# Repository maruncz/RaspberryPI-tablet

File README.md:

RaspberryPI-tablet

just clean project

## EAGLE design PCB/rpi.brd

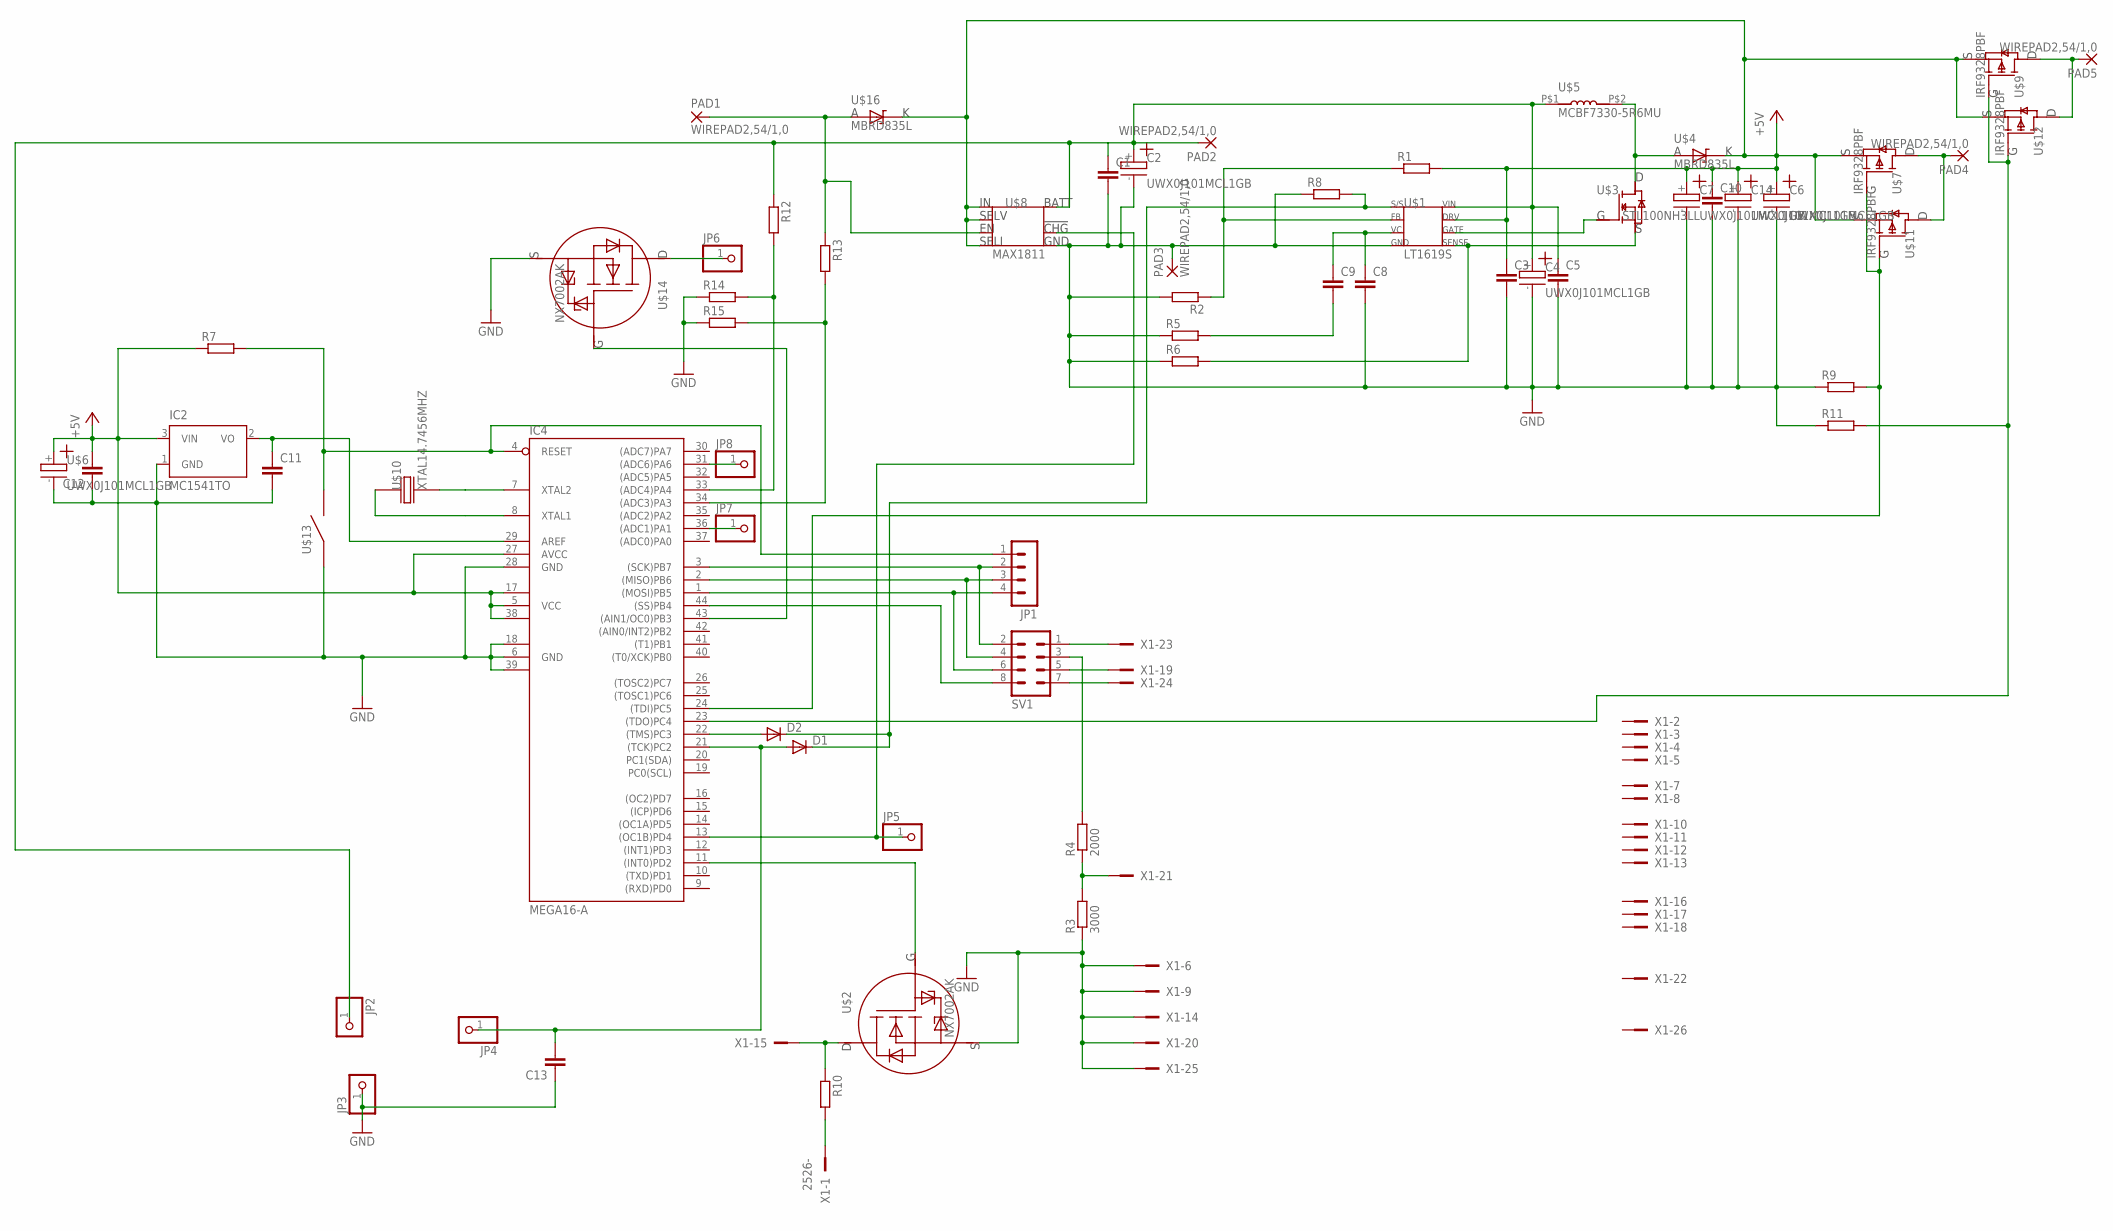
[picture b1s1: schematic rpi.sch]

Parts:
C1, C3, C5, C8, C9, C10, C11, C12, C13: C-EUC1206; C1206
C2, C4, C6, C7, C14: UWX0J101MCL1GB
D1, D2: DIODE-MINIMELF; MINIMELF
IC2: MC1541TO; TO92
IC4: MEGA16-A; TQFP44
JP1: MA04-1
JP2, JP3, JP4, JP5, JP6, JP7, JP8: PINHD-1X1; 1X01
PAD1, PAD2, PAD3, PAD4, PAD5: WIREPAD2,54/1,0; 2,54/1,0
R1, R2, R5, R6, R7, R8, R9, R10, R11, R12, R13, R14, R15: R-EU_R1206; R1206
R3: 3000; R1206
R4: 2000; R1206
SV1: MA04-2
U$1: LT1619S; SO8
U$2, U$14: NX7002AK; SOT23
U$3: STL100NH3LL; POWERFLAT6X5
U$4, U$16: MBRD835L; DPAK
U$5: MCBF7330-5R6MU
U$6: UWX0J101MCL1GB
U$7, U$9, U$11, U$12: IRF9328PBF; SO8
U$8: MAX1811; SO8
U$10: XTAL14.7456MHZ; HC49-SMD
U$13: TLACITKO
X1: 2526-; PAK100/2500-26

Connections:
+5V: C3.1, C6.+, C7.+, C10.1, C12.2, C14.+, IC2.3 (VIN), IC4.5 (VCC), IC4.17 (VCC1), IC4.27 (AVCC), IC4.38 (VCC2), R1.2, R7.1, U$1.D2 (DRV), U$4.4 (K), U$6.+, U$7.S, U$7.S2 (S), U$7.S3 (S), U$8.G (IN), U$8.S (SELV), U$8.S2 (SELI), U$9.S, U$9.S2 (S), U$9.S3 (S), U$11.S, U$11.S2 (S), U$11.S3 (S), U$12.S, U$12.S2 (S), U$12.S3 (S), U$16.4 (K)
AREF: C11.1, IC2.2 (VO), IC4.29 (AREF)
GND: C1.2, C2.-, C3.2, C4.-, C5.2, C6.-, C7.-, C8.2, C10.2, C11.2, C12.1, C13.1, C14.-, IC2.1 (GND), IC4.6 (GND), IC4.18 (GND1), IC4.28 (GND), IC4.39 (GND2), JP3.1, PAD3.1, R2.2, R3.1, R5.1, R6.1, R8.1, R9.1, R11.1, R14.1, R15.1, U$1.G (GND), U$2.S, U$6.-, U$8.D3 (GND), U$8.S3 (GND), U$13.P$1, U$13.P$3, U$14.S, X1.6, X1.9, X1.14, X1.20, X1.25
unnamed: R3.2, R4.1, X1.21
unnamed: IC4.34 ((ADC3)PA3), R13.2, R15.2
unnamed: D2.A, IC4.22 ((TMS)PC3)
unnamed: R4.2, SV1.3
unnamed: SV1.7, X1.24
unnamed: IC4.11 ((INT0)PD2), U$2.G
unnamed: R10.2, X1.1
unnamed: R10.1, U$2.D, X1.15
unnamed: IC4.43 ((AIN1/OC0)PB3), U$14.G
unnamed: JP6.1, U$14.D
unnamed: IC4.36 ((ADC1)PA1), JP7.1
unnamed: R1.1, R2.1, U$1.S2 (FB)
unnamed: R6.2, U$1.D4 (SENSE), U$3.1 (S), U$3.2 (S), U$3.3 (S)
unnamed: IC4.31 ((ADC6)PA6), JP8.1
unnamed: IC4.24 ((TDI)PC5), R9.2, U$7.G, U$11.G
unnamed: IC4.33 ((ADC4)PA4), R12.2, R14.2
unnamed: PAD1.1, R13.1, U$8.D2 (EN), U$16.1 (A), U$16.3 (A)
unnamed: U$1.D3 (GATE), U$3.4 (G)
unnamed: C13.2, D1.A, IC4.21 ((TCK)PC2), JP4.1
unnamed: PAD4.1, U$7.D, U$7.D2 (D), U$7.D3 (D), U$7.D4 (D), U$11.D, U$11.D2 (D), U$11.D3 (D), U$11.D4 (D)
unnamed: SV1.5, X1.19
unnamed: SV1.1, X1.23
unnamed: U$3.5 (D), U$4.1 (A), U$4.3 (A), U$5.P$2
unnamed: C9.2, R5.2
unnamed: C8.1, C9.1, U$1.S3 (VC)
unnamed: PAD5.1, U$9.D, U$9.D2 (D), U$9.D3 (D), U$9.D4 (D), U$12.D, U$12.D2 (D), U$12.D3 (D), U$12.D4 (D)
PA3: C1.1, C2.+, C4.+, C5.1, JP2.1, PAD2.1, R12.1, U$1.D (VIN), U$5.P$1, U$8.D4 (BATT)
PB4: IC4.44 ((SS)PB4), SV1.8
PB5: IC4.1 ((MOSI)PB5), JP1.4, SV1.6
PB6: IC4.2 ((MISO)PB6), JP1.3, SV1.4
PC3: D1.C, D2.C, R8.2, U$1.S (S/S)
PC4: IC4.23 ((TDO)PC4), R11.2, U$9.G, U$12.G
PD5: IC4.13 ((OC1B)PD4), JP5.1, U$8.D (!CHG)
RESET: IC4.4 (RESET), JP1.1, R7.2, U$13.P$2, U$13.P$4
SCK: IC4.3 ((SCK)PB7), JP1.2, SV1.2
XTAL1: IC4.8 (XTAL1), U$10.P$1
XTAL2: IC4.7 (XTAL2), U$10.P$2

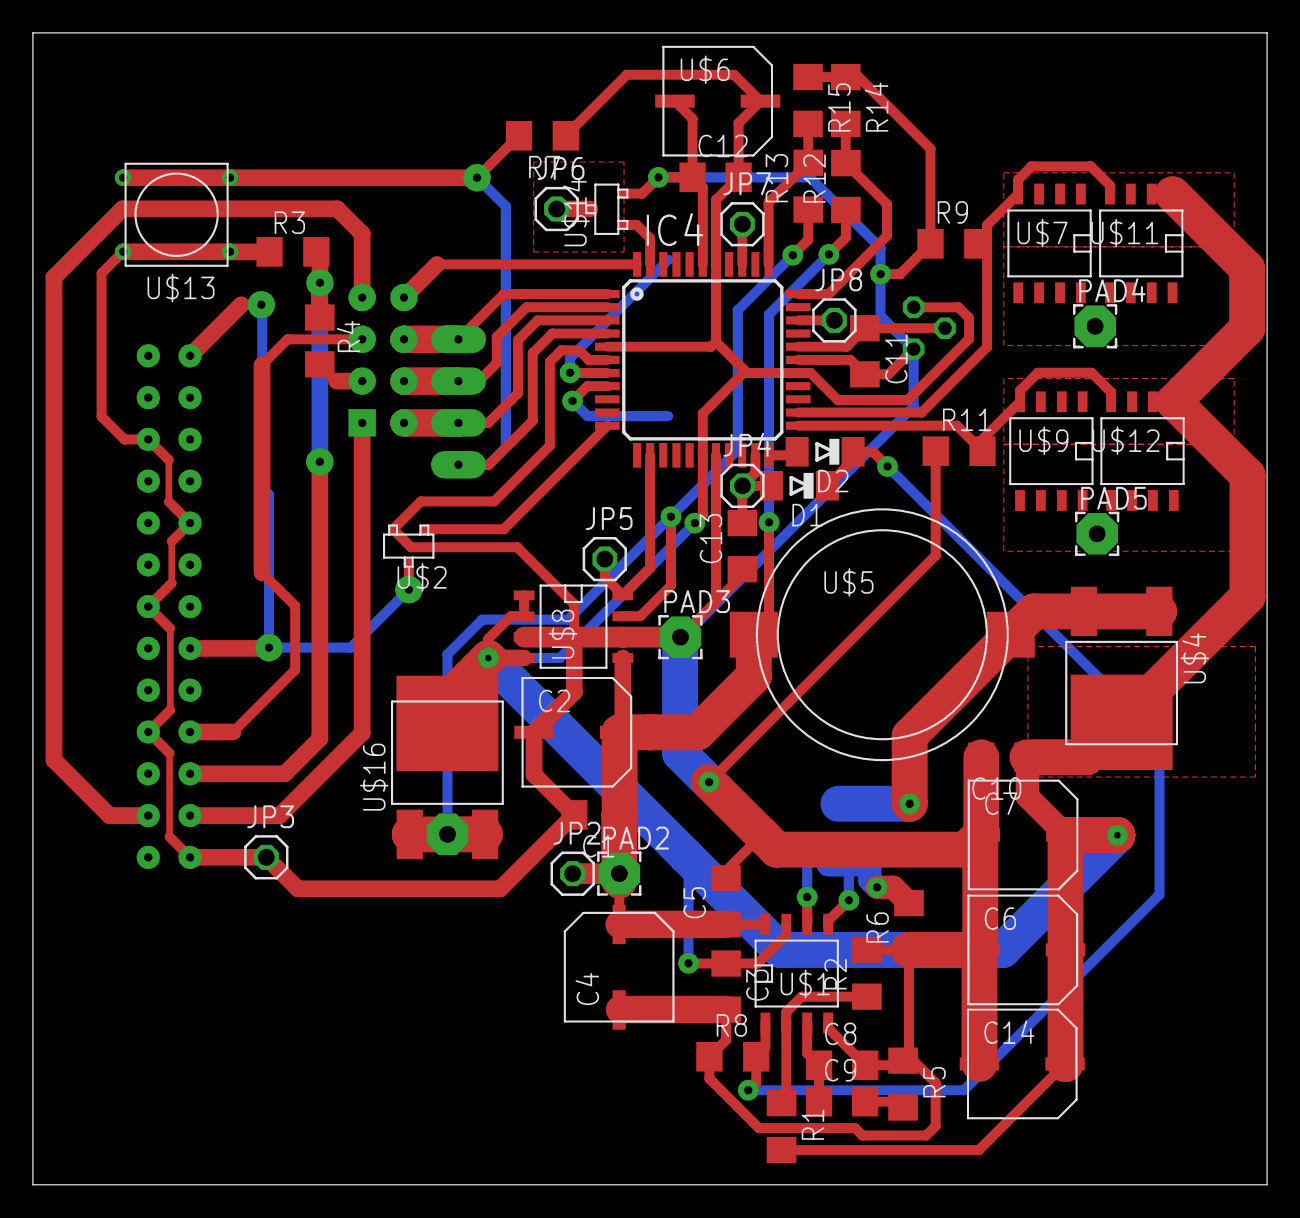
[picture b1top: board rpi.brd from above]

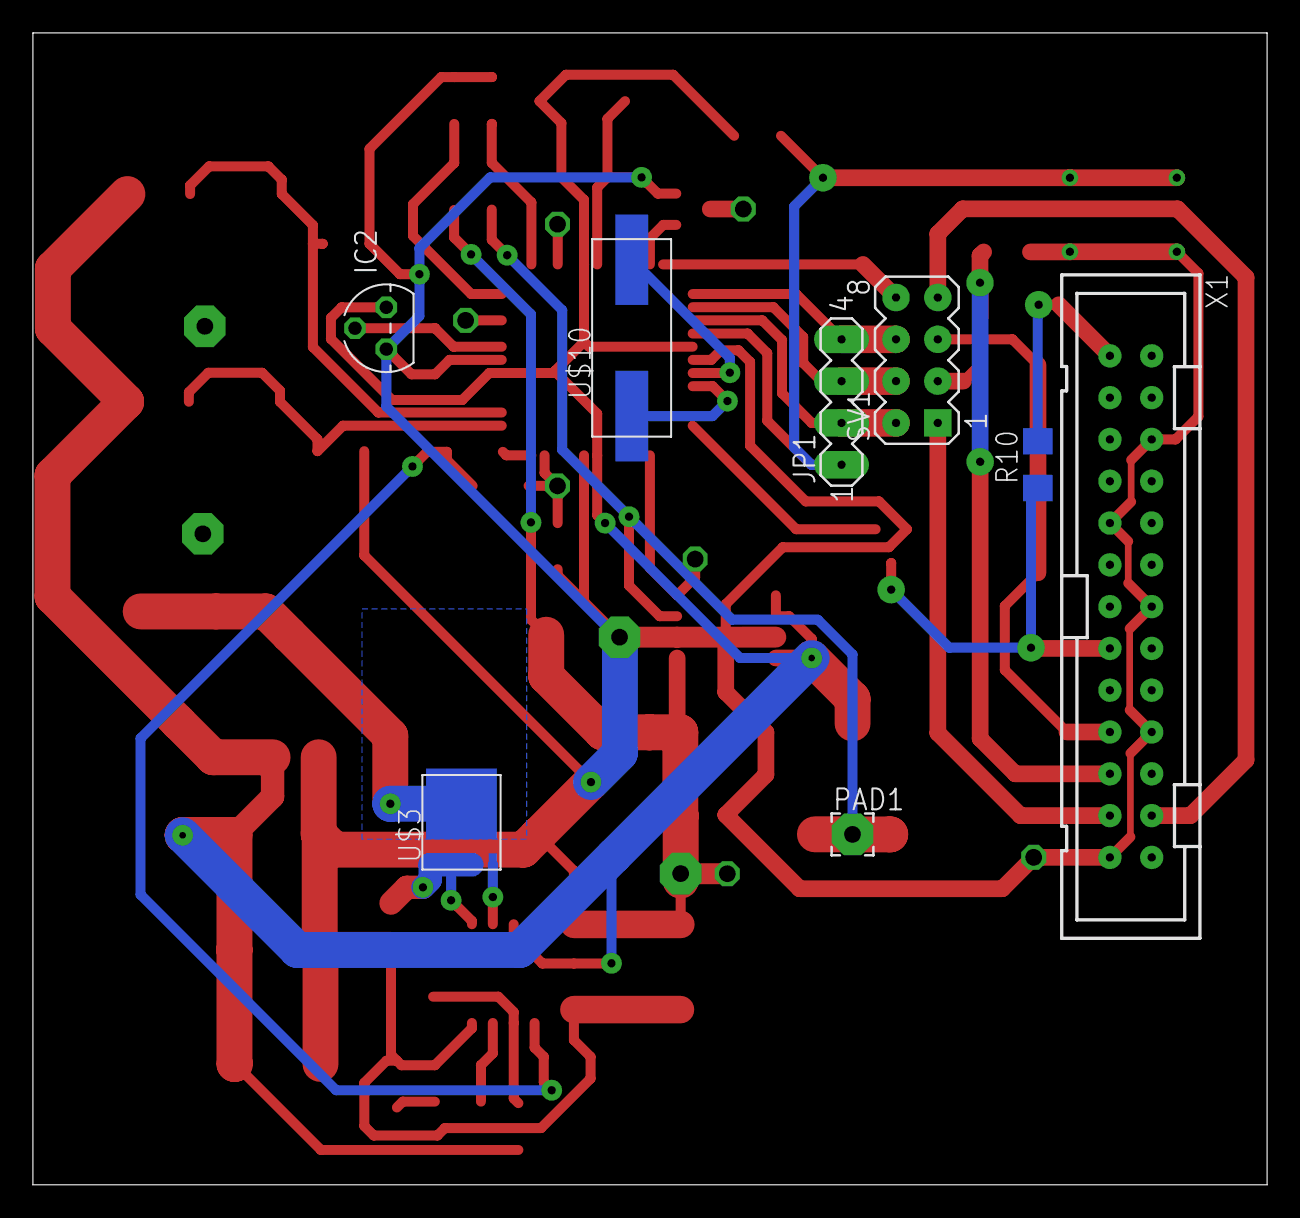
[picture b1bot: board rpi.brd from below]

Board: 2 copper layers, 75.0 x 70.0 mm, 63 parts (8 on the bottom side), 40 nets.

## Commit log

2014-02-09 Initial commit
    Changes to be committed:
    (use "git rm --cached <file>..." to unstage)
    new file: AVR/AVR.cbp
    new file: AVR/AVR.layout
    new file: AVR/Makefile
    new file: AVR/Makefile~
2014-02-09 On branch master Changes to be committed: (use "git reset HEAD <file>..." to unstage)
    new file: README.md
2014-02-09 On branch master Changes to be committed: (use "git reset HEAD <file>..." to unstage)
    modified: README.md
    Untracked files:
    (use "git add <file>..." to include in what will be committed)
    README.md~
2014-02-09 On branch master Changes to be committed: new file: RaspberryPI/Crystal_button_cancel.svg new file: RaspberryPI/Ps_GreekCross.svg modified: RaspberryPI/RaspberryPI.pro modified: RaspberryPI/Raspberry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
    Changes not staged for commit:
    deleted: AVR/Makefile~
    deleted: AVR/bin/Release/AVR.eep
    deleted: AVR/bin/Release/AVR.elf
    deleted: AVR/bin/Release/AVR.hex
    deleted: AVR/bin/Release/AVR.lock
2014-02-09 On branch master modified: RaspberryPI/RaspberryPI.pro.user modified: RaspberryPI/main.cpp modified: RaspberryPI/mainwindow.cpp modified: RaspberryPI/mainwindow.h modified: RaspberryPI/mainwindow.ui
2014-02-09 On branch master Changes to be committed: modified: AVR/main.c
2014-02-09 On branch master modified: RaspberryPI/mainwindow.cpp modified: RaspberryPI/mainwindow.h modified: RaspberryPI/mainwindow.ui
2014-02-09 On branch master modified: AVR/Makefile modified: AVR/Makefile~ deleted: AVR/bin/Release/AVR.eep deleted: AVR/bin/Release/AVR.elf deleted: AVR/bin/Release/AVR.hex deleted: AVR/bin/Release/AVR.lock de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
2014-02-09 On branch master deleted: AVR/Makefile~ modified: RaspberryPI/RaspberryPI.pro.user modified: RaspberryPI/mainwindow.cpp modified: RaspberryPI/mainwindow.h
2014-02-09 On branch master deleted: AVR/Makefile~ modified: RaspberryPI/mainwindow.cpp modified: RaspberryPI/mainwindow.h
2014-02-10 On branch master modified: RaspberryPI/RaspberryPI.pro.user modified: RaspberryPI/mainwindow.cpp modified: RaspberryPI/mainwindow.h
2014-02-10 On branch master modified: RaspberryPI/RaspberryPI.pro.user modified: RaspberryPI/mainwindow.h
2014-02-10 On branch master modified: AVR/AVR.layout modified: AVR/main.c
2014-02-10 On branch master modified: RaspberryPI/mainwindow.cpp
2014-02-10 On branch master modified: RaspberryPI/RaspberryPI.pro.user modified: RaspberryPI/mainwindow.cpp modified: RaspberryPI/mainwindow.ui
2014-02-10 On branch master modified: AVR/main.c
2014-02-11 On branch master modified: AVR/AVR.cbp modified: AVR/AVR.layout
2014-02-11 On branch master modified: RaspberryPI/RaspberryPI.pro.user modified: RaspberryPI/mainwindow.cpp
2014-02-22 On branch master modified: RaspberryPI/RaspberryPI.pro.user modified: RaspberryPI/mainwindow.cpp modified: RaspberryPI/mainwindow.h modified: RaspberryPI/mainwindow.ui
2014-02-22 On branch master modified: RaspberryPI/RaspberryPI.pro.user new file: rpi/eagle.epf new file: rpi/rpi.brd new file: rpi/rpi.pro new file: rpi/rpi.sch new file: tablet.lbr
2014-02-22 On branch master renamed: rpi/eagle.epf -> PCB/eagle.epf renamed: rpi/rpi.brd -> PCB/rpi.brd renamed: rpi/rpi.pro -> PCB/rpi.pro renamed: rpi/rpi.sch -> PCB/rpi.sch
2014-02-23 On branch master modified: PCB/eagle.epf modified: PCB/rpi.brd modified: PCB/rpi.sch modified: RaspberryPI/RaspberryPI.pro.user
2014-02-28 On branch master modified: PCB/eagle.epf modified: PCB/rpi.brd modified: RaspberryPI/RaspberryPI.pro.user modified: RaspberryPI/mainwindow.cpp
2014-03-02 On branch master modified: AVR/AVR.layout modified: AVR/Makefile
2014-03-02 On branch master modified: PCB/eagle.epf modified: PCB/rpi.brd modified: RaspberryPI/RaspberryPI.pro.user
2014-03-04 On branch master modified: PCB/eagle.epf modified: RaspberryPI/RaspberryPI.pro.user modified: RaspberryPI/mainwindow.cpp
2014-03-06 On branch master modified: PCB/eagle.epf new file: RaspberryPI-shutdown/RaspberryPI-shutdown.pro new file: RaspberryPI-shutdown/main.cpp modified: RaspberryPI/RaspberryPI.pro.user modified: Raspberry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
2014-03-06 On branch master modified: RaspberryPI-shutdown/RaspberryPI-shutdown.pro deleted: RaspberryPI/RaspberryPI.pro.user
2014-03-08 On branch master modified: PCB/eagle.epf modified: PCB/rpi.brd modified: PCB/rpi.sch modified: RaspberryPI/mainwindow.cpp modified: RaspberryPI/mainwindow.h modified: RaspberryPI/mainwindow.ui
2014-03-08 On branch master modified: PCB/eagle.epf modified: PCB/rpi.brd modified: PCB/rpi.sch
2014-03-16 On branch master modified: PCB/eagle.epf modified: PCB/rpi.brd modified: PCB/rpi.sch modified: RaspberryPI-shutdown/RaspberryPI-shutdown.pro modified: RaspberryPI/RaspberryPI.pro
2014-03-18 On branch master modified: PCB/eagle.epf modified: RaspberryPI-shutdown/main.cpp modified: RaspberryPI/RaspberryPI.pro new file: RaspberryPI/info_screen.cpp new file: RaspberryPI/info_screen.h new fi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
2014-03-18 On branch master modified: RaspberryPI/RaspberryPI.pro new file: RaspberryPI/hwinfo.cpp new file: RaspberryPI/hwinfo.h modified: RaspberryPI/info_screen.cpp modified: RaspberryPI/info_screen.h modifi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
2014-03-18 On branch master modified: RaspberryPI/hwinfo.h modified: RaspberryPI/info_screen.cpp modified: RaspberryPI/info_screen.h
2014-03-18 On branch master modified: RaspberryPI/hwinfo.cpp modified: RaspberryPI/hwinfo.h modified: RaspberryPI/info_screen.cpp modified: RaspberryPI/info_screen.h
2014-03-18 On branch master modified: RaspberryPI/hwinfo.cpp modified: RaspberryPI/hwinfo.h modified: RaspberryPI/info_screen.cpp modified: RaspberryPI/mainwindow.cpp
2014-03-18 On branch master modified: RaspberryPI/hwinfo.cpp
2014-03-23 On branch master modified: PCB/eagle.epf modified: RaspberryPI/hwinfo.cpp modified: RaspberryPI/info_screen.cpp modified: RaspberryPI/info_screen.h modified: RaspberryPI/mainwindow.cpp modified: Rasp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
2014-03-26 On branch master modified: PCB/eagle.epf modified: RaspberryPI/hwinfo.cpp modified: RaspberryPI/hwinfo.h modified: RaspberryPI/info_screen.cpp modified: RaspberryPI/mainwindow.cpp
2014-03-29 On branch master modified: RaspberryPI/RaspberryPI.pro modified: RaspberryPI/hwinfo.h new file: RaspberryPI/idle_detect.cpp new file: RaspberryPI/idle_detect.h modified: RaspberryPI/info_screen.cpp m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
2014-03-29 On branch master modified: RaspberryPI/idle_detect.cpp modified: RaspberryPI/idle_detect.h modified: RaspberryPI/mainwindow.cpp modified: RaspberryPI/mainwindow.h modified: RaspberryPI/mainwindow.ui
2014-03-30 On branch master modified: PCB/eagle.epf modified: RaspberryPI/rpi.cpp modified: RaspberryPI/rpi.h
2014-04-06 On branch master modified: PCB/eagle.epf modified: RaspberryPI/idle_detect.cpp modified: RaspberryPI/idle_detect.h modified: RaspberryPI/info_screen.ui modified: RaspberryPI/mainwindow.cpp modified: 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
2014-04-12 On branch master modified: PCB/eagle.epf modified: RaspberryPI/mainwindow.cpp modified: RaspberryPI/mainwindow.h modified: RaspberryPI/mainwindow.ui modified: RaspberryPI/rpi.cpp modified: RaspberryP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
2014-04-12 On branch master modified: RaspberryPI/RaspberryPI.pro modified: RaspberryPI/mainwindow.cpp modified: RaspberryPI/rpi.cpp modified: RaspberryPI/rpi.h
2014-04-13 On branch master modified: RaspberryPI/mainwindow.cpp modified: RaspberryPI/mainwindow.h modified: RaspberryPI/rpi.cpp modified: RaspberryPI/rpi.h
2014-04-15 On branch master modified: RaspberryPI/mainwindow.cpp modified: RaspberryPI/mainwindow.h
2014-04-21 On branch master modified: PCB/eagle.epf modified: RaspberryPI/mainwindow.cpp modified: RaspberryPI/mainwindow.h modified: RaspberryPI/rpi.cpp modified: RaspberryPI/rpi.h
2014-04-27 On branch master modified: AVR/AVR.layout modified: AVR/Makefile modified: AVR/main.c
2014-04-27 On branch master modified: PCB/eagle.epf modified: RaspberryPI/idle_detect.cpp modified: RaspberryPI/idle_detect.h modified: RaspberryPI/mainwindow.cpp modified: RaspberryPI/mainwindow.h modified: Ra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
2014-04-27 On branch master modified: RaspberryPI/main.cpp modified: RaspberryPI/mainwindow.cpp modified: RaspberryPI/mainwindow.h modified: RaspberryPI/mainwindow.ui modified: RaspberryPI/rpi.cpp modified: Ras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
2014-06-12 modified: RaspberryPI/main.cpp modified: RaspberryPI/mainwindow.cpp modified: RaspberryPI/mainwindow.h modified: RaspberryPI/rpi.cpp modified: RaspberryPI/rpi.h
2014-06-12 On branch master modified: AVR/AVR.cbp modified: AVR/AVR.layout modified: AVR/main.c
2014-06-12 On branch master deleted: AVR/AVR.cbp deleted: AVR/AVR.layout
2014-06-12 On branch master new file: AVR/AVR.cbp
2018-06-02 nejaky bordel
